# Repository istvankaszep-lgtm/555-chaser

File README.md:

# 555-chaser
this is a led chaser with red leds.

How to use it: to power it you need max a 5V output and also you need 2 female to male jumper wire.
For power source you can use an arduino or get an usb cable and cut one end of it and connect them using the jumper wires
and then plug te usb cable in a 5V charger or in a laptop/pc.

I made this proiect to test out hack club/blueprint and to learn how to use kicad, also this is my very first proiect.

[led cheser.csv](https://github.com/user-attachments/files/29943318/led.cheser.csv)

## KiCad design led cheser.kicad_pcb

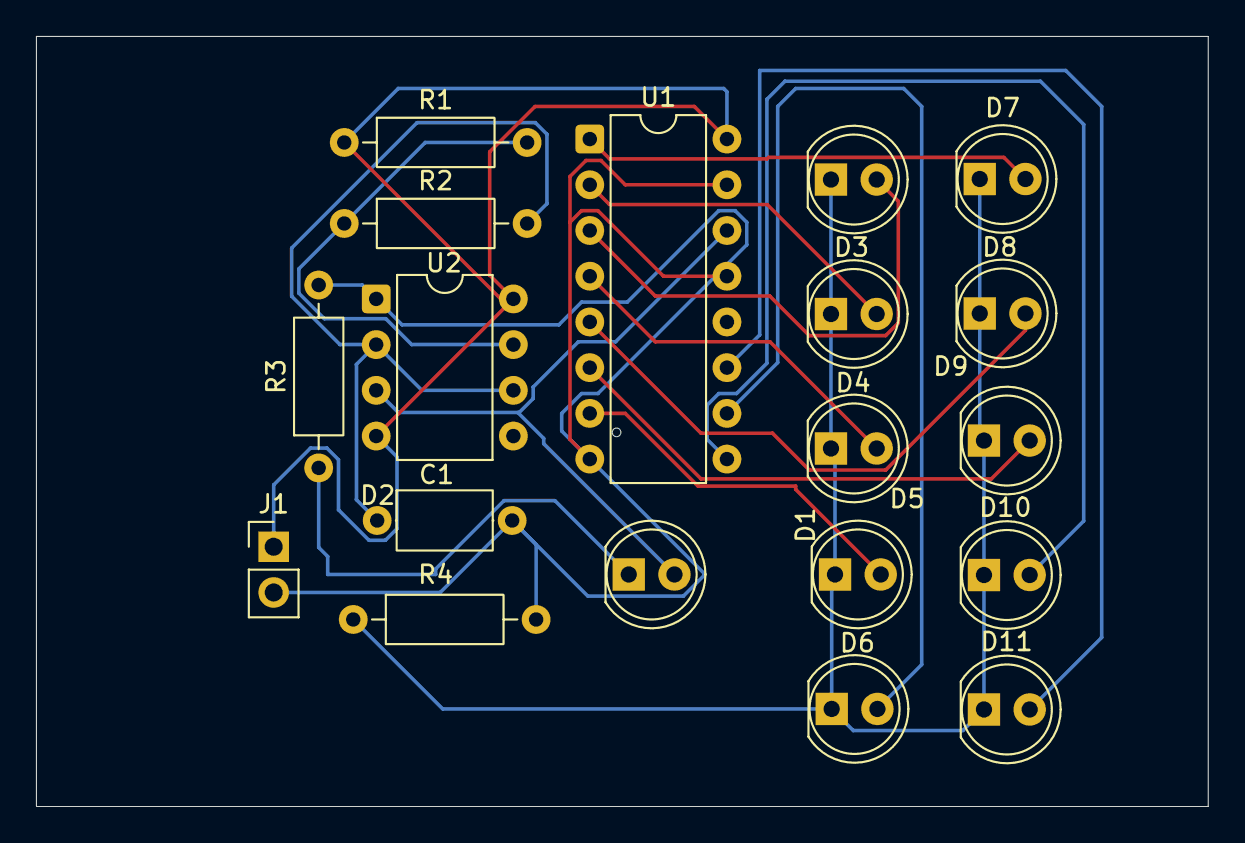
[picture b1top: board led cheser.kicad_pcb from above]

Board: 2 copper layers, 65.1 x 42.8 mm, 19 parts (0 on the bottom side), 17 nets.

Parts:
C1: C_Small_US; C_Axial_L5.1mm_D3.1mm_P7.50mm_Horizontal
D1, D2, D3, D4, D5, D6, D7, D8, D9, D10, D11: LED; LED_D5.0mm
J1: Conn_01x02_Pin; PinHeader_1x02_P2.54mm_Vertical
R1, R2: R10k; R_Axial_DIN0207_L6.3mm_D2.5mm_P10.16mm_Horizontal
R3, R4: R150; R_Axial_DIN0207_L6.3mm_D2.5mm_P10.16mm_Horizontal
U1: 4017; DIP-16_W7.62mm
U2: NE555P; DIP-8_W7.62mm

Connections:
+5V: J1.1, R1.1, U1.16 (VDD), U2.4 (~RST), U2.8 (VCC)
GND: C1.2, J1.2, R3.2, R4.2, U1.8 (VSS), U1.13 (CKEN), U1.15 (Reset), U2.1 (GND)
unnamed: D1.2 (A), U1.14 (CLK), U2.3 (OUT)
unnamed: D1.1 (K), R3.1
unnamed: D2.2 (A), U1.3 (Q0)
unnamed: D3.2 (A), U1.2 (Q1)
unnamed: D4.2 (A), U1.4 (Q2)
unnamed: D5.2 (A), U1.7 (Q3)
unnamed: D6.2 (A), U1.10 (Q4)
unnamed: D7.2 (A), U1.1 (Q5)
unnamed: D8.2 (A), U1.5 (Q6)
unnamed: D9.2 (A), U1.6 (Q7)
unnamed: D10.2 (A), U1.9 (Q8)
unnamed: D2.1 (K), D3.1 (K), D4.1 (K), D5.1 (K), D6.1 (K), D7.1 (K), D8.1 (K), D9.1 (K), D10.1 (K), D11.1 (K), R4.1
unnamed: D11.2 (A), U1.11 (Q9)
unnamed: R1.2, R2.1, U2.7 (DISCH)
unnamed: C1.1, R2.2, U2.2 (TRIG), U2.6 (THRES)

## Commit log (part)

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2026-04-10 README.md
